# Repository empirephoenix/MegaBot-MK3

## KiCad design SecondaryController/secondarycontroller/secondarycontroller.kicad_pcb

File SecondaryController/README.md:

*Backup parsing for brake
*Steering servo emulation
*emergency brake controll

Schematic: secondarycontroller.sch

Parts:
CF15: C; C_Rect_L41.5mm_W13.0mm_P37.50mm_MKS4
D1: DIODE; D_5W_P12.70mm_Horizontal
J1: Receiver; PinHeader_1x03_P2.54mm_Vertical
J2: Conn_01x07_Female; PinSocket_1x07_P2.54mm_Vertical
J3: VIN; PinHeader_1x02_P2.54mm_Vertical
J4: APA102C; PinHeader_1x04_P2.54mm_Vertical
J5: I2C BUS; PinHeader_1x02_P2.54mm_Vertical
Potentiometer1: Conn_01x03_Male; JST_EH_B03B-EH-A_1x03_P2.50mm_Vertical
SW1: Calibrate; SW_PUSH_6mm
SW2: Reset; SW_PUSH_6mm
XA1: Arduino_Uno_Shield

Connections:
unnamed: CF15.1, D1.2, J1.1, J2.2, J2.6, J4.1, Potentiometer1.1, SW1.2, SW2.1, XA1.GND2
unnamed: CF15.2, Potentiometer1.2, XA1.A0
unnamed: D1.1, J3.1
unnamed: J1.3, XA1.D12
unnamed: J2.1, J2.7, J4.4, Potentiometer1.3, XA1.5V1 (5V)
unnamed: J2.3, XA1.D11
unnamed: J2.4, XA1.D10 (D10_CS)
unnamed: J2.5, XA1.D8
unnamed: J3.2, XA1.VIN
unnamed: J4.2, XA1.D4
unnamed: J4.3, XA1.D5
unnamed: J5.1, XA1.SDA
unnamed: J5.2, XA1.SCL
unnamed: SW1.1, XA1.D13
unnamed: SW2.2, XA1.RST1 (RESET)

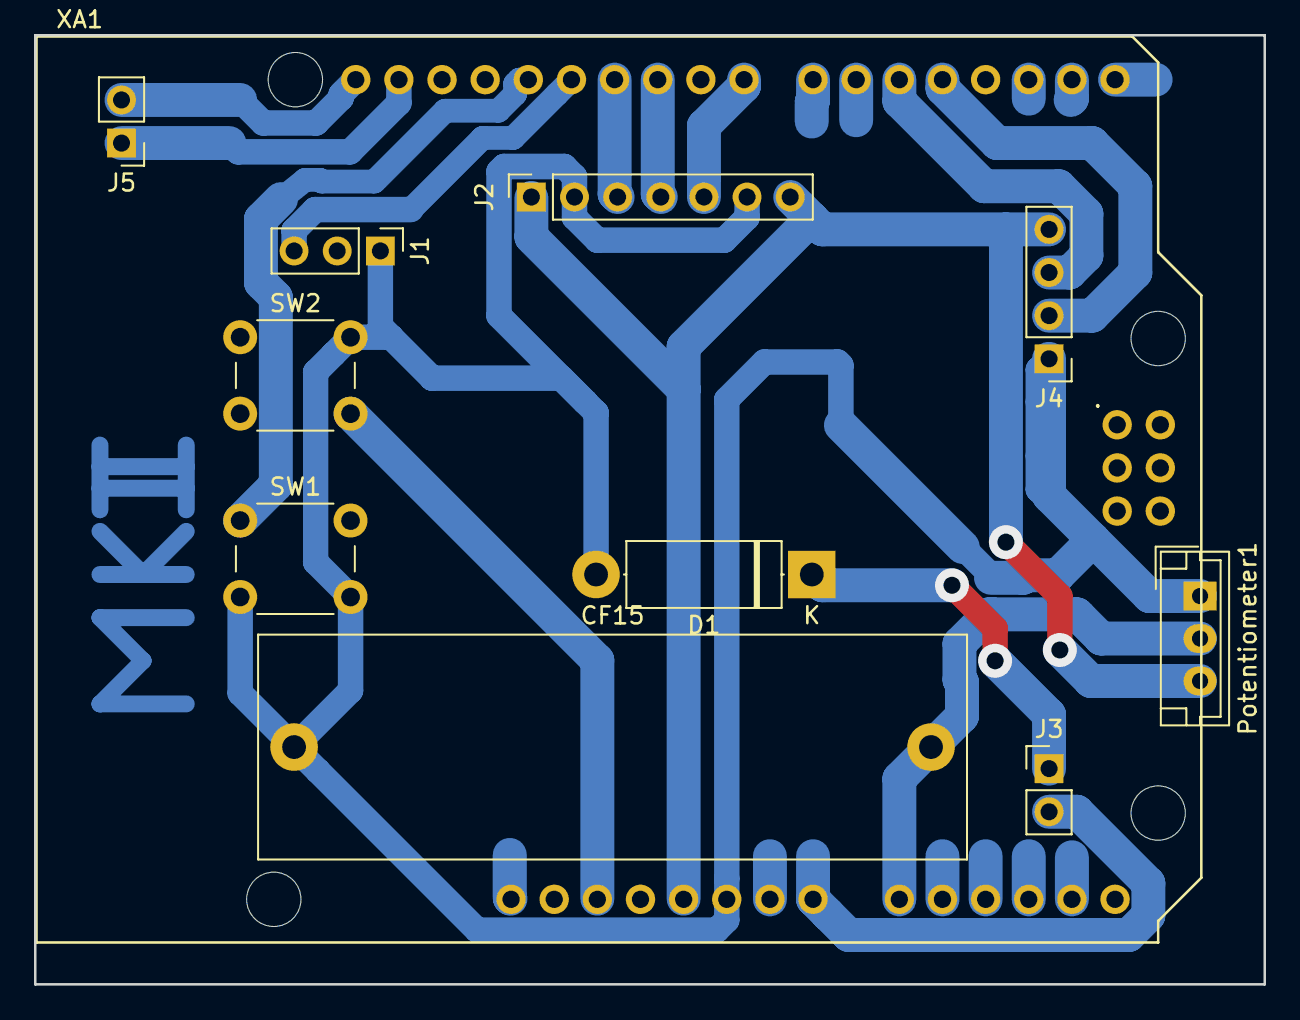
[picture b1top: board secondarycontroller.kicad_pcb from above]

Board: 2 copper layers, 72.4 x 55.9 mm, 11 parts (0 on the bottom side), 15 nets.

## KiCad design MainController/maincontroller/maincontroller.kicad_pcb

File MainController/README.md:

*Input parsing for most functions
*Controll of all MotorControllers
*Normal Braking Relay controll
*Basic light controll
*Parsing of Speed answer from MotorControllers
*Limits ensurance mode
*Constant Speed / Constant Power switch
*Drift mode
*Parsing of steering channel for electical differential

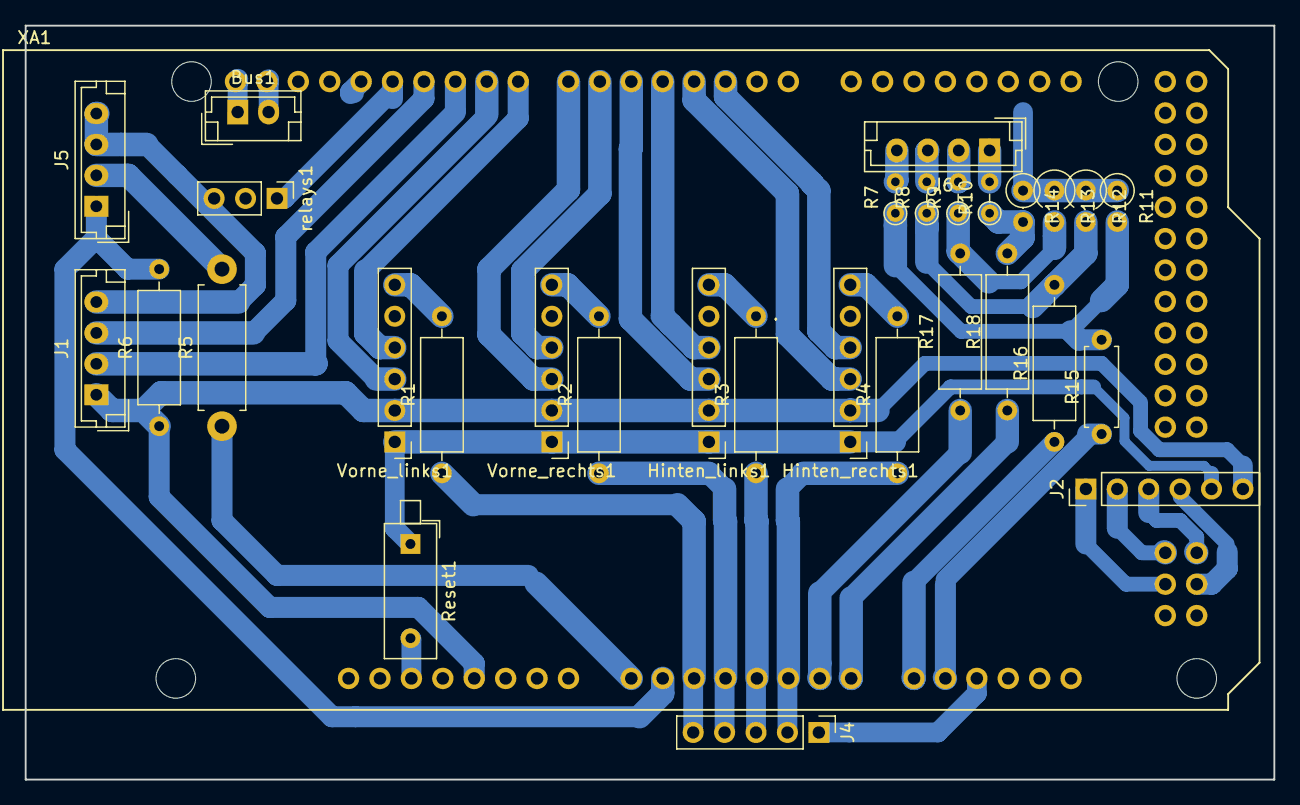
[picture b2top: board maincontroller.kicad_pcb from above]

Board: 2 copper layers, 101.0 x 61.0 mm, 31 parts (0 on the bottom side), 45 nets.

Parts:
Bus1: Conn_01x02; JST_EH_B02B-EH-A_1x02_P2.50mm_Vertical
Hinten_links1: MCP4725; PinHeader_1x06_P2.54mm_Vertical
Hinten_rechts1: MCP4725; PinHeader_1x06_P2.54mm_Vertical
J1: LED; JST_EH_B04B-EH-A_1x04_P2.50mm_Vertical
J2: Receiver; PinHeader_1x06_P2.54mm_Vertical
J4: Analog_Motor; PinHeader_1x05_P2.54mm_Vertical
J5: OneWire; JST_EH_B04B-EH-A_1x04_P2.50mm_Vertical
J6: Hall_In; JST_EH_B04B-EH-A_1x04_P2.50mm_Vertical
R1, R2, R3, R4: R380; R_Axial_DIN0309_L9.0mm_D3.2mm_P12.70mm_Horizontal
R5: R215; R_Axial_DIN0411_L9.9mm_D3.6mm_P12.70mm_Horizontal
R6: R4K7; R_Axial_DIN0309_L9.0mm_D3.2mm_P12.70mm_Horizontal
R7, R8, R9, R10: R30k; R_Axial_DIN0204_L3.6mm_D1.6mm_P2.54mm_Vertical
R11, R14: R2k7; R_Axial_DIN0207_L6.3mm_D2.5mm_P2.54mm_Vertical
R12, R13: R2k7; R_Axial_DIN0309_L9.0mm_D3.2mm_P2.54mm_Vertical
R15: R4k7; R_Axial_DIN0207_L6.3mm_D2.5mm_P7.62mm_Horizontal
R16, R17, R18: R4k7; R_Axial_DIN0309_L9.0mm_D3.2mm_P12.70mm_Horizontal
Reset1: SW_Push; SW_DIP_SPSTx01_Piano_10.8x4.1mm_W7.62mm_P2.54mm
Vorne_links1: MCP4725; PinHeader_1x06_P2.54mm_Vertical
Vorne_rechts1: MCP4725; PinHeader_1x06_P2.54mm_Vertical
XA1: Arduino_Mega2560_Shield
relays1: Conn_01x05_Female; PinHeader_1x03_P2.54mm_Vertical

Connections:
unnamed: Bus1.1, XA1.SCL
unnamed: Bus1.2, XA1.SDA
unnamed: Hinten_links1.1, Hinten_rechts1.1, J1.4, J2.5, J5.3, J5.4, R11.1, R12.1, R13.1, R14.1, Reset1.1, Vorne_links1.1, Vorne_rechts1.1, relays1.3
unnamed: Hinten_links1.2, Hinten_rechts1.2, J1.1, J2.6, R6.1, Vorne_links1.2, Vorne_rechts1.2, XA1.5V1
unnamed: Hinten_links1.3, XA1.D5
unnamed: Hinten_links1.4, XA1.D4
unnamed: Hinten_links1.6, R3.2
unnamed: Hinten_rechts1.3, XA1.D3
unnamed: Hinten_rechts1.4, XA1.D2
unnamed: Hinten_rechts1.6, R4.2
unnamed: J1.2, XA1.D10
unnamed: J1.3, XA1.D11
unnamed: J2.1, XA1.D52
unnamed: J2.2, XA1.D50
unnamed: J2.3, XA1.D51
unnamed: J2.4, XA1.D53
unnamed: J4.1, XA1.A10
unnamed: J4.2, R4.1, XA1.A5
unnamed: J4.3, R3.1, XA1.A4
unnamed: J4.4, R2.1, XA1.A3
unnamed: J4.5, R1.1, XA1.A2
unnamed: J5.1, R6.2, XA1.A1
unnamed: J5.2, R5.2
unnamed: J6.1, R10.2
unnamed: J6.2, R9.2
unnamed: J6.3, R8.2
unnamed: J6.4, R7.2
unnamed: R1.2, Vorne_links1.6
unnamed: R2.2, Vorne_rechts1.6
unnamed: R5.1, XA1.A0
unnamed: R10.1, R14.2, R18.2
unnamed: R7.1, R11.2, R15.2
unnamed: R8.1, R12.2, R16.2
unnamed: R9.1, R13.2, R17.2
unnamed: R15.1, XA1.A9
unnamed: R16.1, XA1.A8
unnamed: R17.1, XA1.A6
unnamed: R18.1, XA1.A7
unnamed: Reset1.2, XA1.RST1
unnamed: Vorne_links1.3, XA1.D9
unnamed: Vorne_links1.4, XA1.D8
unnamed: Vorne_rechts1.3, XA1.D7
unnamed: Vorne_rechts1.4, XA1.D6
unnamed: XA1.D12, relays1.1
unnamed: XA1.D13, relays1.2

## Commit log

2018-06-22 commit images for MK2 build
2018-06-22 initial parsing and setup code
2018-06-22 Initial Secondary
2018-06-27 added variable delta, added rc reading, added calibration mode
2018-07-04 eclipse project setup
2018-07-04 Status LED
2018-07-04 Added header to Secondary and cleaned uup project
2018-07-04 Fixed potentially fuckup
2018-07-04 Finished up steering control and feedback LED
2018-07-10 Successfully achived controllable voltage output
2018-07-10 Added color defines
2018-07-13 updated led library
2018-07-13 (hopefully) final commit
2018-07-14 SoftWire works ™
2018-07-21 Status LEDs, DACs & some other stuff
2018-07-31 Implemented brake, reverse & throttle control
2018-08-22 Added iButton support
2018-09-05 Added Pinout diagram
2018-09-05 Adapted secondary controller
2018-09-05 Added keys new processing of them
2018-09-19 improved steering behaviour vor battery supply
2018-09-28 Revert "improved steering behaviour vor battery supply"
    This reverts commit b01f26e62653c0908f2af07a8078ff6bd909d31d.
2018-09-28 Code Cleaning
2018-10-03 improved code quality and disabled reverse untill stopped
2018-10-05 kicad initial for main controller
2018-10-10 SecondaryController first layout
2018-10-10 main controller pcb
2018-10-11 removed 5v in, use reciver power instead, simplified relay connector, added reverse pin to motorconnector
2018-10-17 Clean Up defines and remap to new Boardlayout
2018-10-19 Meh, doesnt work
2018-10-19 Finished PCB Secondary
2018-10-24 Update PIN definition for new Layerdesign
2018-10-31 fixed relay pins
2018-11-03 secondary as done
2018-11-03 new secondary controller pcb design
2018-11-04 main rework
2018-11-04 secondary code fixes
2018-11-04 secondary better pcb design
2018-11-06 secondary controller mk2
2018-11-14 replaced averaging with median calculations
2018-11-21 arduino mega datasheet
2018-11-21 initial hall sensor impl
2018-11-21 adjusted gitignore
2018-11-21 wip speed limiter
2018-12-05 speed limiter v2
